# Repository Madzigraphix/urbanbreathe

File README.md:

Group Members and roles:

1. Dickson Mbogo - Program Developer
2. Elisha Jilo - Electrical Systems Developer
3. Shem Koech - Mechanical Designer
4. Masika - Supervisor

# UrbanBreathe

Overview
An embedded system designed to monitor ambient air conditions in real time. It captures data on key pollutants and environmental parameters to assess air quality, classify hazard levels, and log or transmit data for analysis and response.

Working

Data Acquisition
The system uses environmental sensors to measure:

Particulate Matter (PM2.5, PM10)

Carbon Monoxide (CO)

Nitrogen Dioxide (NO₂)

Temperature and Humidity

Signal Processing
Raw analog/digital data from sensors is processed through a microcontroller. Noise is filtered out, and readings are normalized and scaled.

Air Quality Index Calculation
The processed values are mapped to standardized AQI ranges. The system calculates an overall air quality score based on pollutant concentrations using a weighted formula.

Classification
The AQI value is categorized into levels (e.g., Good, Moderate, Unhealthy). These levels guide public awareness or automated responses.

Data Handling

Logged locally to memory or SD card

Optionally transmitted to a remote server or cloud via Wi-Fi/GSM

Continuous Monitoring
The system performs regular sampling at set intervals. The loop ensures ongoing air status tracking and historical trend capture.

Trello link
https://trello.com/b/yV4AvyV6/team

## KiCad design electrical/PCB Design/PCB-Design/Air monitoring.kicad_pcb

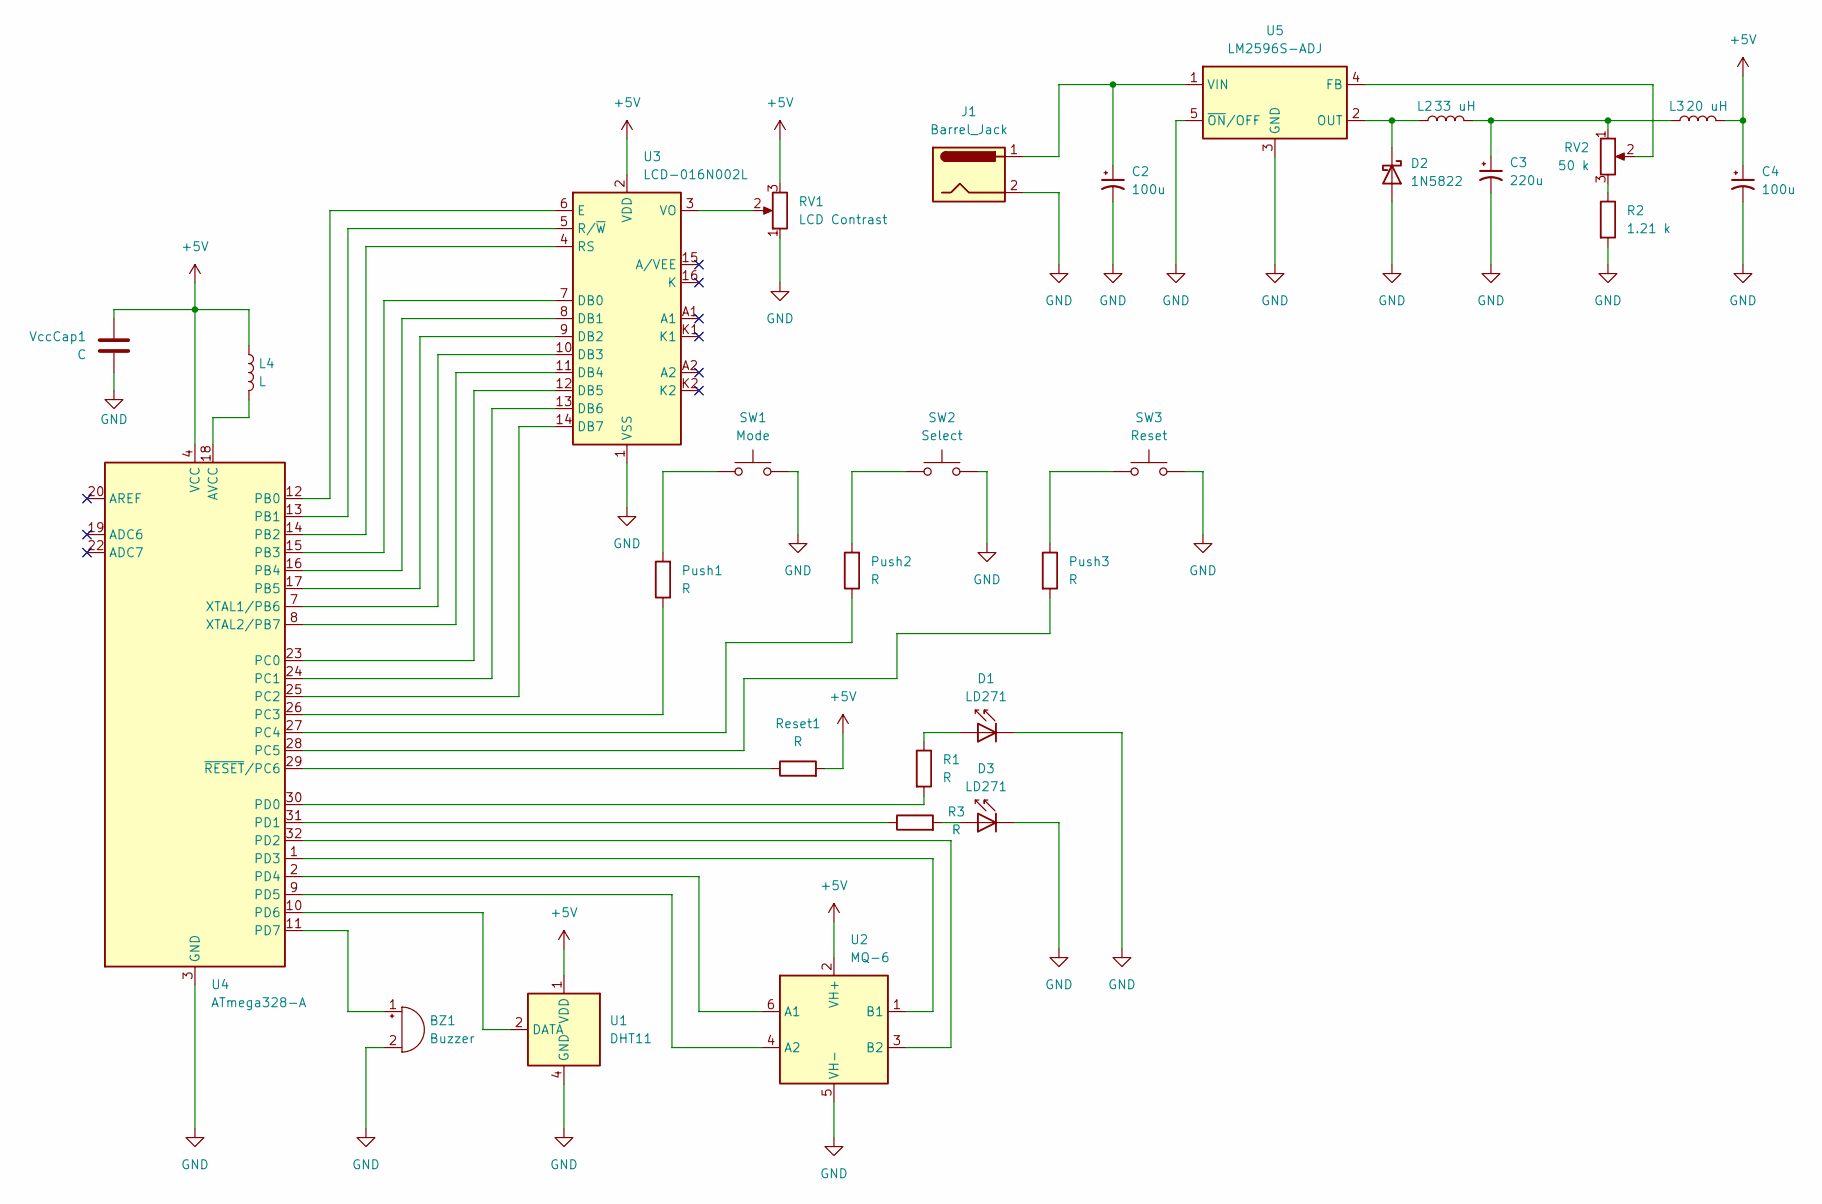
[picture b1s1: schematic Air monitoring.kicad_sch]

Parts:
BZ1: Buzzer; MagneticBuzzer_ProSignal_ABT-410-RC
C2: 100u; CP_Elec_8x10
C3: 220u; CP_Elec_10x10
C4: 100u; CP_Elec_6.3x5.4
D1: LD271; LED_VCCLite_5381H3_6.35x6.35mm
D2: 1N5822; D_5W_P10.16mm_Horizontal
D3: LD271; LED_VCCLite_5381H5_6.35x6.35mm
J1: Barrel_Jack; BarrelJack_Horizontal
L2: 33 uH; L_Bourns_SRR1260
L3: 20 uH; L_Bourns_SRR1260
L4: L; L_Axial_L6.6mm_D2.7mm_P10.16mm_Horizontal_Vishay_IM-2
Push1, Push2, Push3: R; R_0805_2012Metric
R1: R; R_1206_3216Metric
R2: 1.21 k; R_1206_3216Metric
R3: R; R_0805_2012Metric_Pad1.20x1.40mm_HandSolder
RV1: LCD Contrast; Potentiometer_Bourns_3314G_Vertical
RV2: 50 k; Potentiometer_Bourns_3296Y_Vertical
Reset1: R; R_0805_2012Metric
SW1: Mode; SW_SPST_PTS647_Sx50
SW2: Select; SW_SPST_PTS647_Sx50
SW3: Reset; SW_SPST_PTS647_Sx50
U1: DHT11; Aosong_DHT11_5.5x12.0_P2.54mm
U2: MQ-6
U3: LCD-016N002L
U4: ATmega328-A; TQFP-32_7x7mm_P0.8mm
U5: LM2596S-ADJ; TO-263-5_TabPin3
VccCap1: C; CP_Radial_D4.0mm_P1.50mm

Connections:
+5V: C4.1, L3.2, L4.1, RV1.3, Reset1.2, U1.1 (VDD), U2.2 (VH+), U3.2 (VDD), U4.4 (VCC), U4.6 (VCC), VccCap1.2
GND: BZ1.2 (-), C2.2, C3.2, C4.2, D1.1 (K), D2.2 (A), D3.1 (K), J1.2, R2.2, RV1.1, SW1.2, SW2.2, SW3.2, U1.4 (GND), U2.5 (VH-), U3.1 (VSS), U4.3 (GND), U4.5 (GND), U4.21 (GND), U5.3 (GND), U5.5 (~ON/OFF), VccCap1.1
unnamed: BZ1.1 (+), U4.11 (PD7)
unnamed: C3.1, L2.2, L3.1, RV2.1
unnamed: D1.2 (A), R1.1
unnamed: D2.1 (K), L2.1, U5.2 (OUT)
unnamed: D3.2 (A), R3.2
unnamed: Push1.2, SW1.1
unnamed: Push2.2, SW2.1
unnamed: Push3.1, SW3.1
unnamed: R2.1, RV2.3
unnamed: U1.2 (DATA), U4.10 (PD6)
unnamed: U2.6 (A1), U4.2 (PD4)
unnamed: U2.4 (A2), U4.9 (PD5)
unnamed: U2.1 (B1), U4.1 (PD3)
unnamed: U2.3 (B2), U4.32 (PD2)
unnamed: U3.7 (DB0), U4.15 (PB3)
unnamed: U3.8 (DB1), U4.16 (PB4)
unnamed: U3.9 (DB2), U4.17 (PB5)
unnamed: U3.10 (DB3), U4.7 (XTAL1/PB6)
unnamed: U3.11 (DB4), U4.8 (XTAL2/PB7)
unnamed: U3.12 (DB5), U4.23 (PC0)
unnamed: U3.13 (DB6), U4.24 (PC1)
unnamed: U3.14 (DB7), U4.25 (PC2)
unnamed: U3.6 (E), U4.12 (PB0)
unnamed: U3.4 (RS), U4.14 (PB2)
unnamed: U3.5 (R/~W), U4.13 (PB1)
unnamed: RV1.2, U3.3 (VO)
unnamed: L4.2, U4.18 (AVCC)
unnamed: Push1.1, U4.26 (PC3)
unnamed: Push2.1, U4.27 (PC4)
unnamed: Push3.2, U4.28 (PC5)
unnamed: R1.2, U4.30 (PD0)
unnamed: R3.1, U4.31 (PD1)
unnamed: Reset1.1, U4.29 (~RESET/PC6)
unnamed: RV2.2, U5.4 (FB)
unnamed: C2.1, J1.1, U5.1 (VIN)

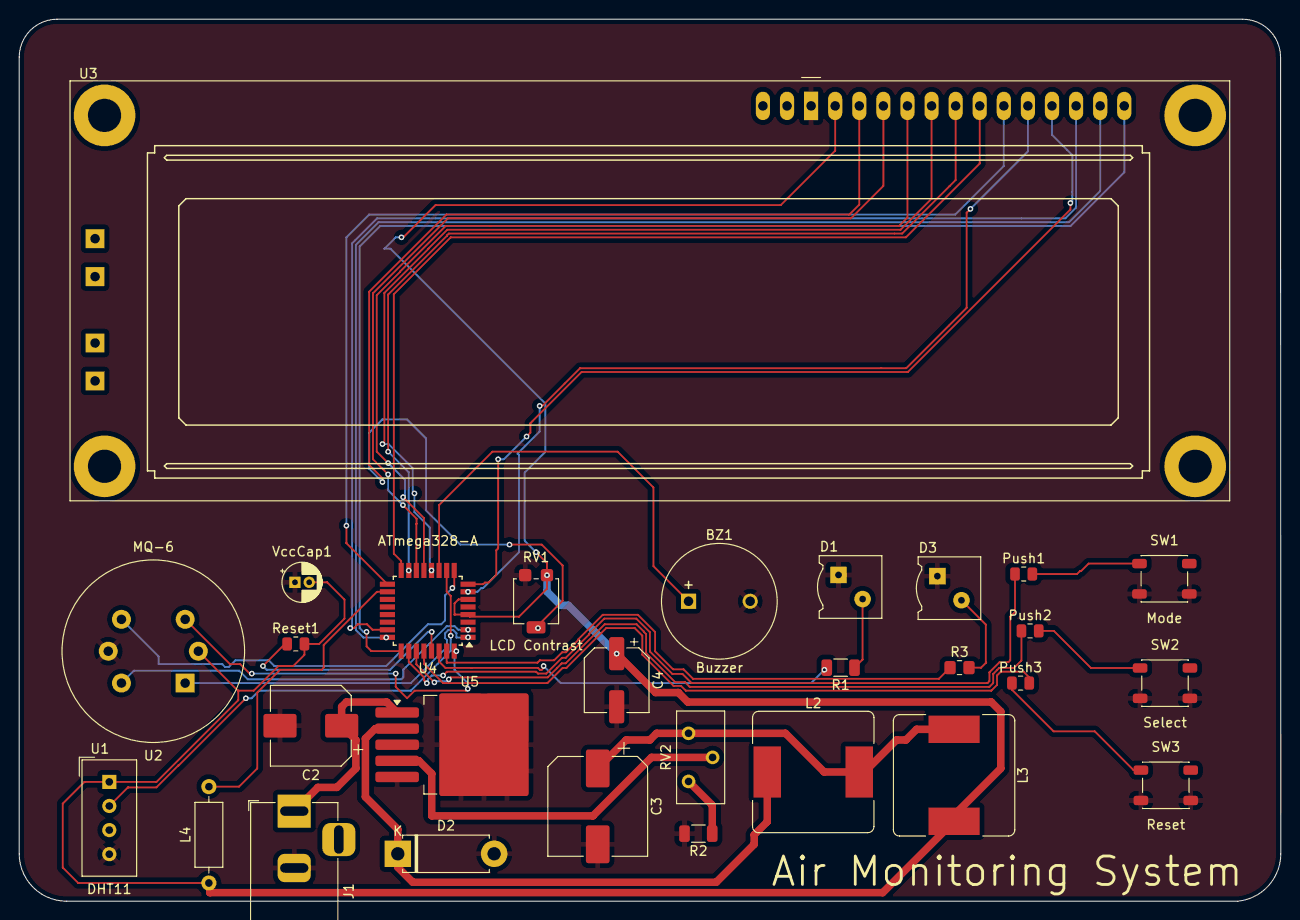
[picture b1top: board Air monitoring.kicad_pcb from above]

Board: 2 copper layers, 133.0 x 93.0 mm, 29 parts (0 on the bottom side), 37 nets.

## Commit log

2025-06-17 added elctrical
2025-06-17 picture
2025-06-18 Add mechanical components
2025-06-18 Add STEP file and mechanical design image
2025-06-18 Add STEP and design image to mechanical folder
2025-06-22 Update: mechanical design version 2
2025-06-22 Updated second version of the design
2025-06-22 Add: Updated Design upload
2025-06-22 Created file
2025-06-22 Updated the mechanical design
2025-06-22 Add pcb
2025-06-22 Added PCB design files
2025-06-22 Added new Assembly image
